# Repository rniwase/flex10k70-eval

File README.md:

# flex10k70-eval
PCB design data for evaluation of the Altera FLEX 10K70 (EPF10K70RC240).

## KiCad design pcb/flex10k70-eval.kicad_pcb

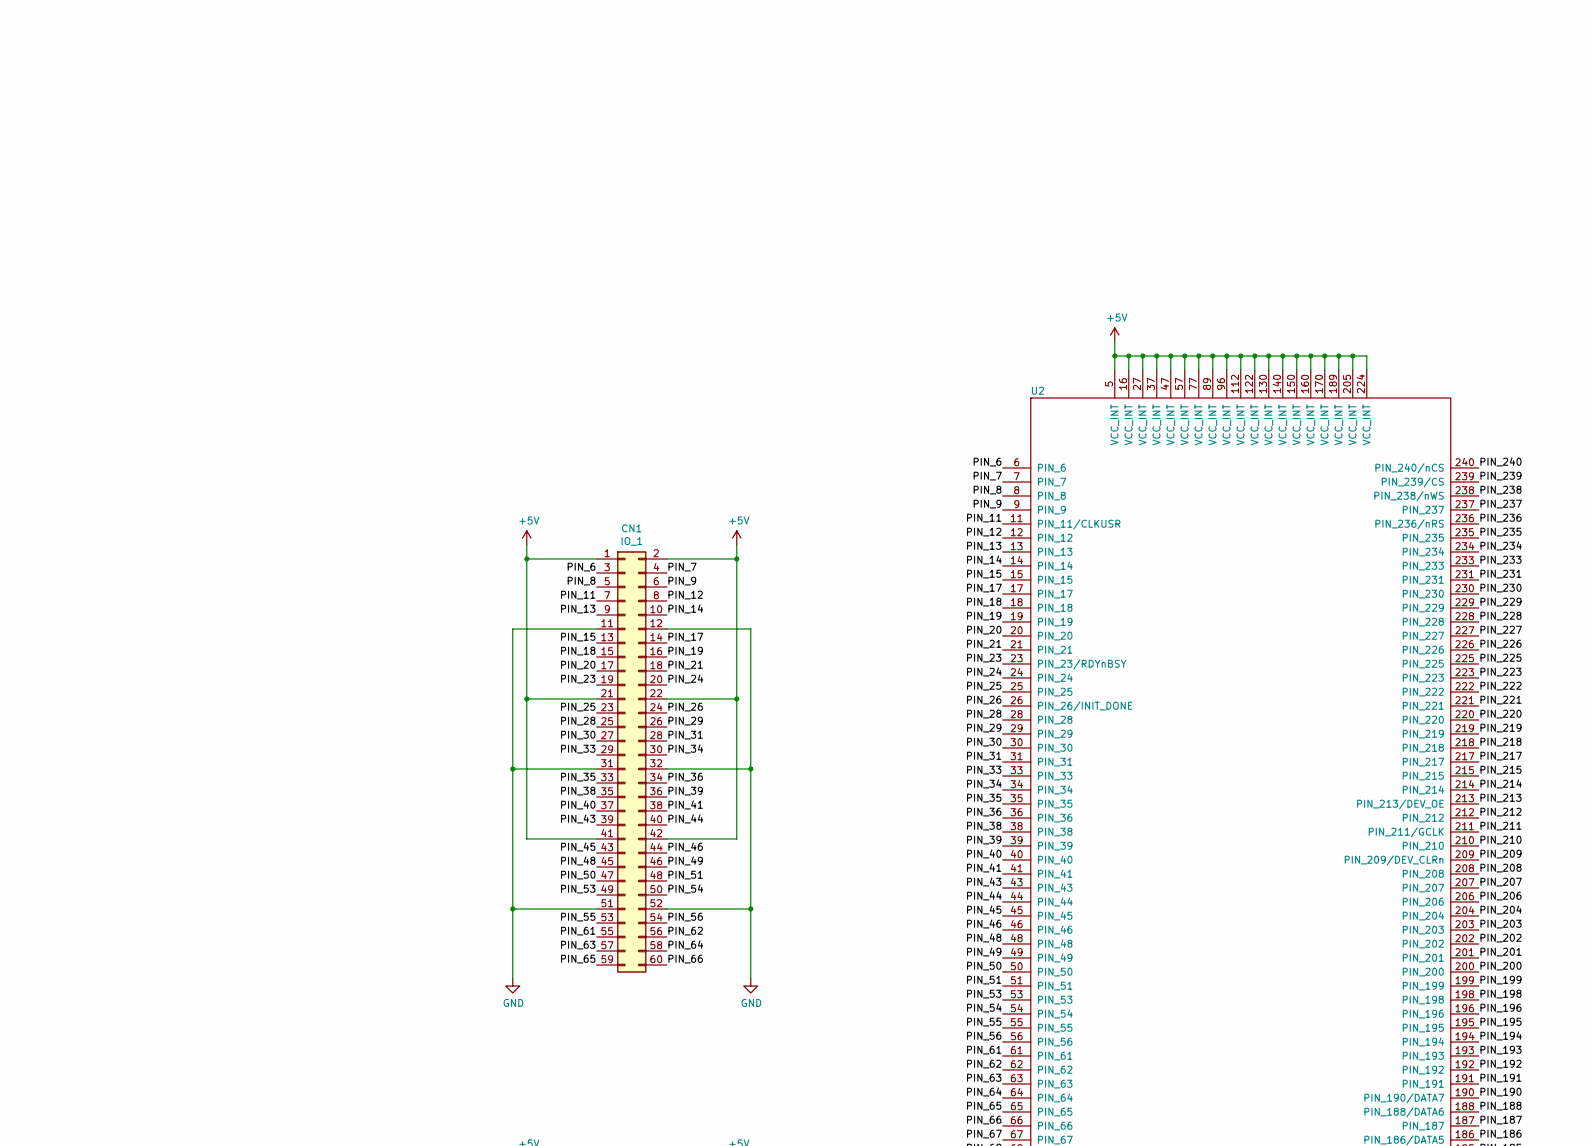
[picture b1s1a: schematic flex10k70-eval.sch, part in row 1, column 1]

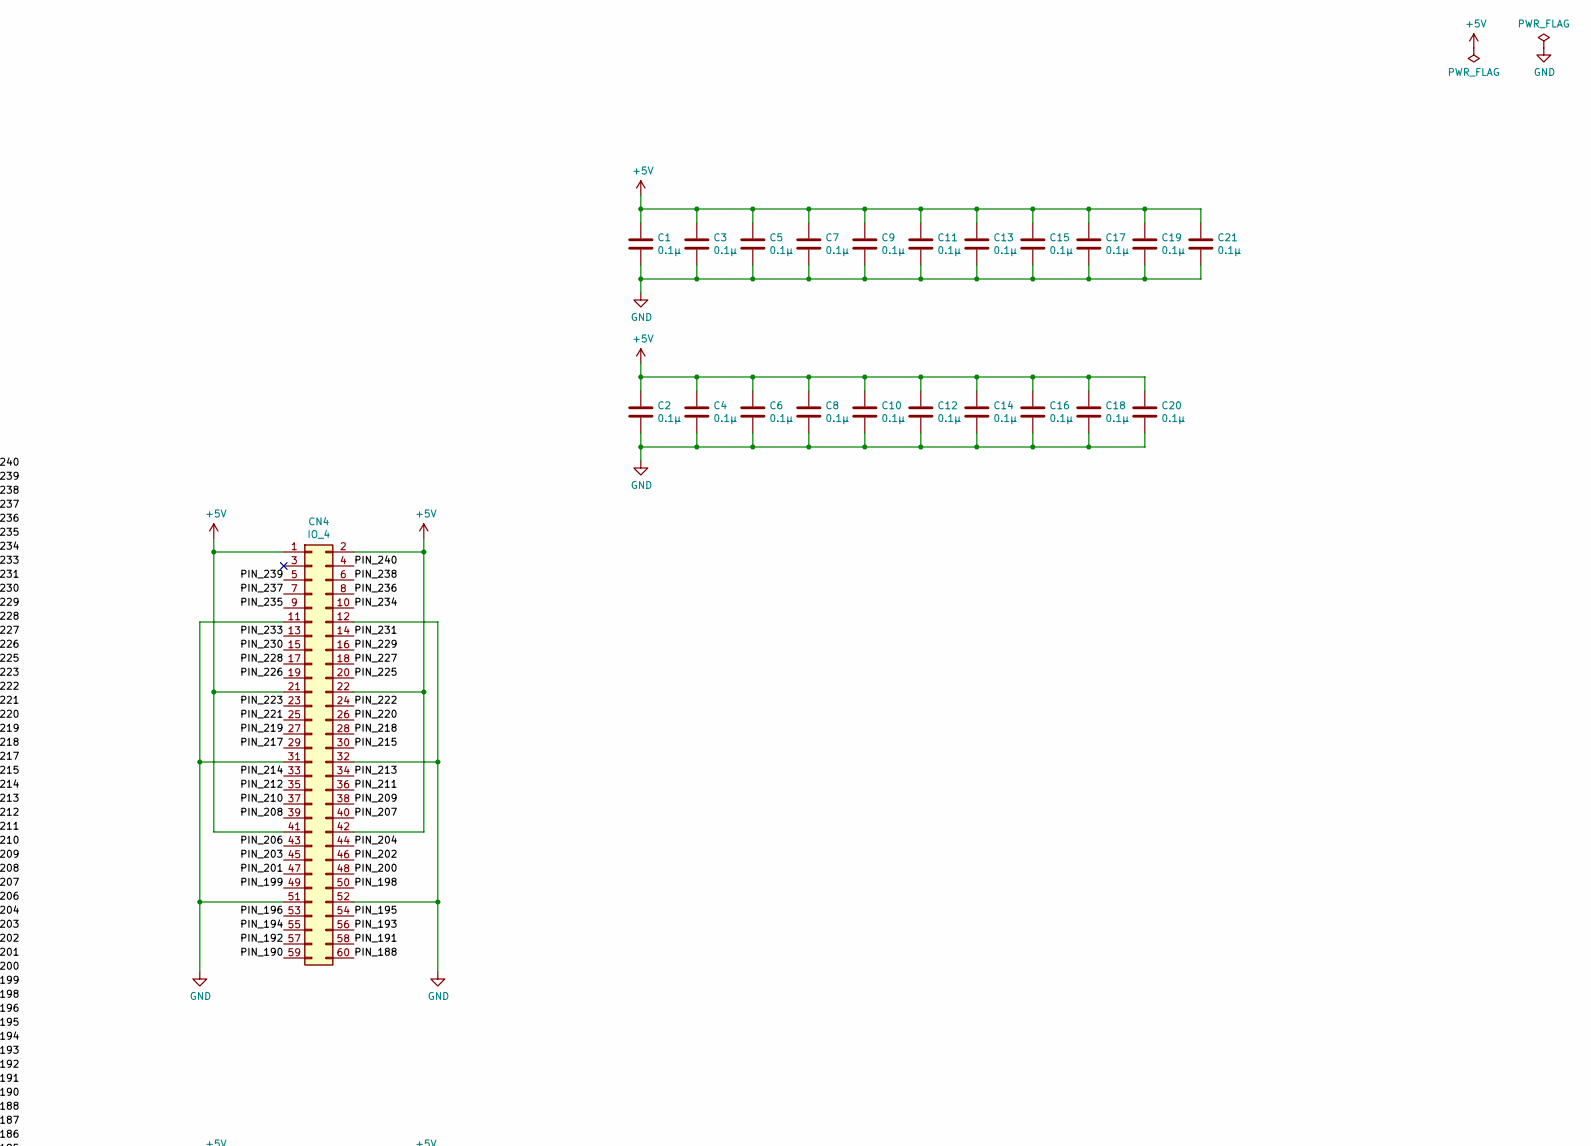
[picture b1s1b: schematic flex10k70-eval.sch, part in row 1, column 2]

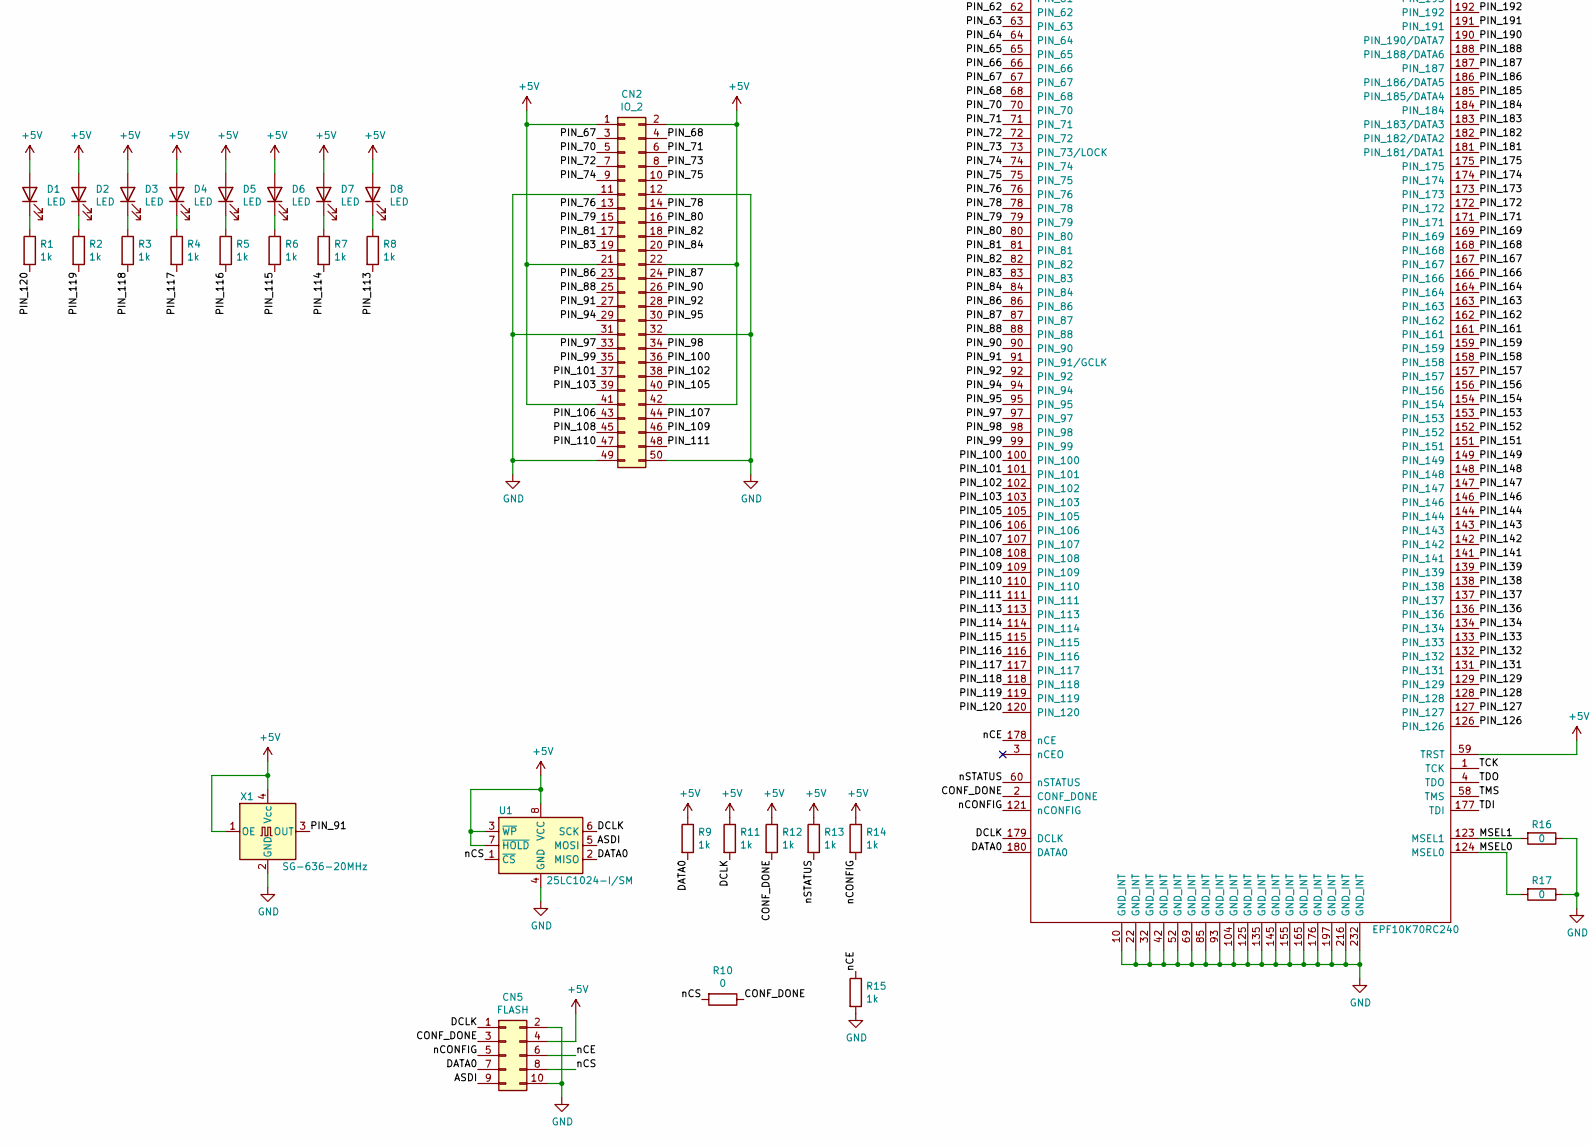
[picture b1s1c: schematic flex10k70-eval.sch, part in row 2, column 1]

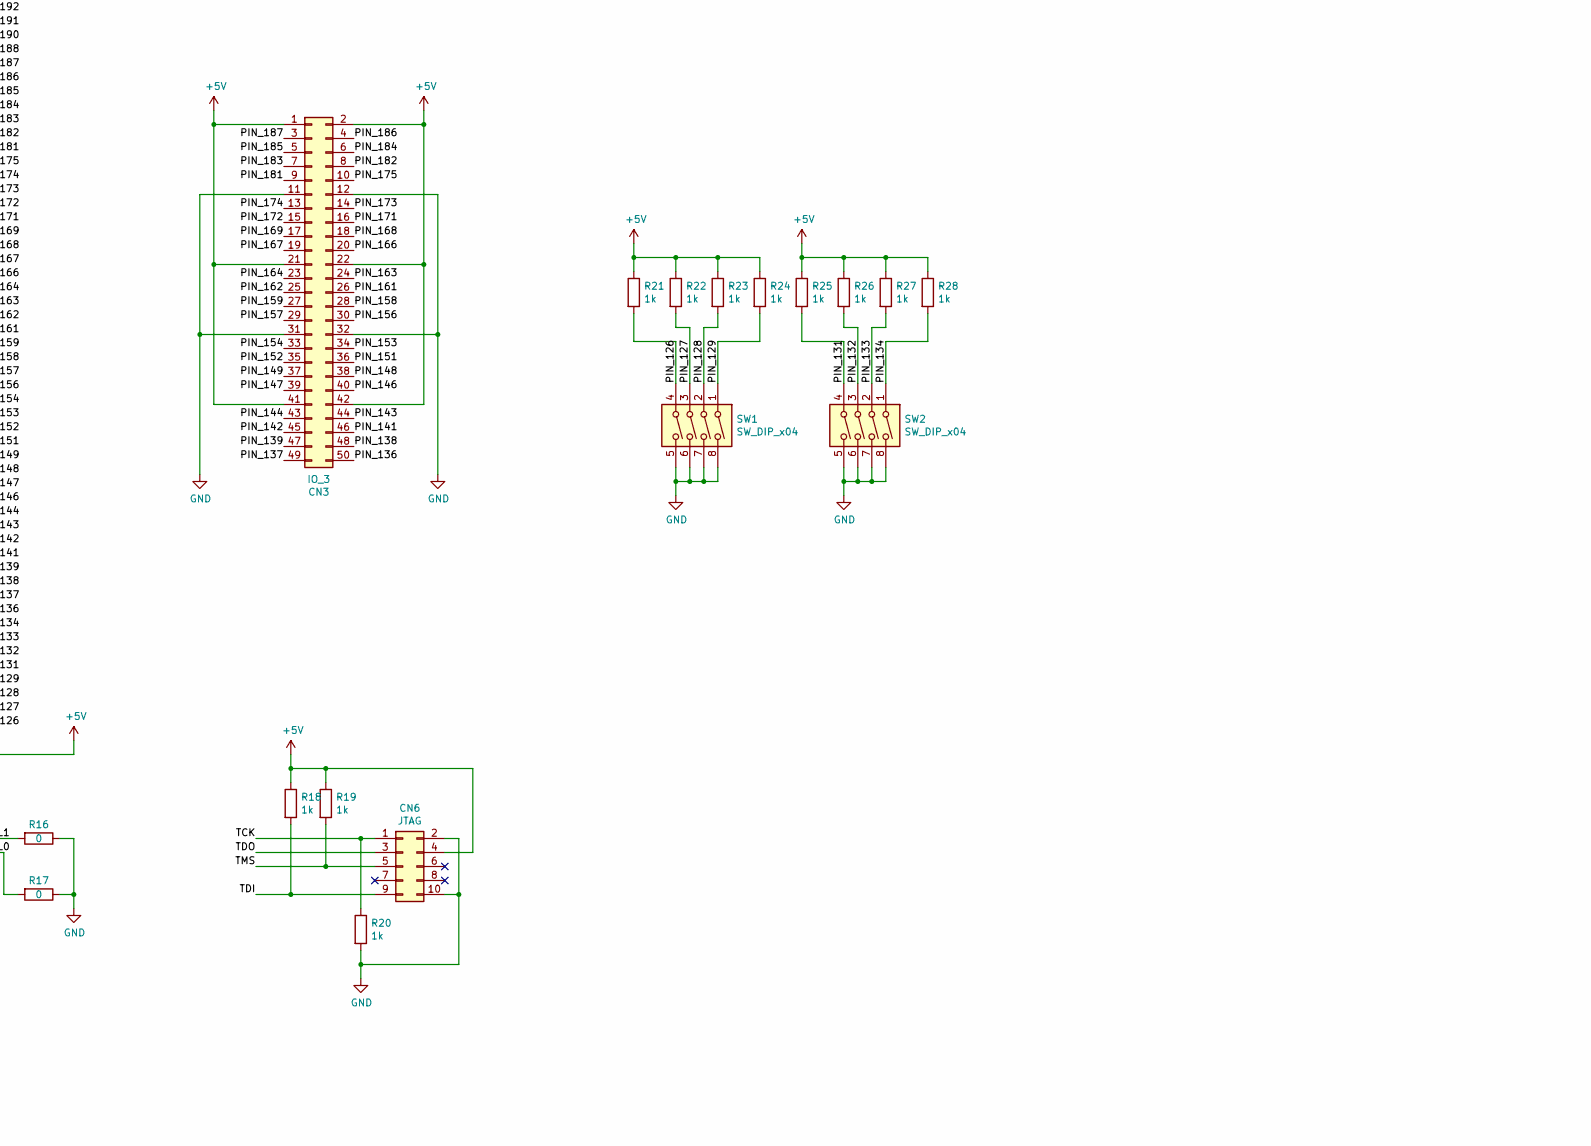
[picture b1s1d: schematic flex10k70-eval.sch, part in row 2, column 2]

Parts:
C1, C2, C3, C4, C5, C6, C7, C8, C9, C10, C11, C12, C13, C14, C15, C16, C17, C18, C19, C20, C21: 0.1μ; C_0603_1608Metric
CN1: IO_1; PinHeader_2x30_P2.54mm_Vertical_SMD
CN2: IO_2; PinHeader_2x25_P2.54mm_Vertical_SMD
CN3: IO_3; PinHeader_2x25_P2.54mm_Vertical_SMD
CN4: IO_4; PinHeader_2x30_P2.54mm_Vertical_SMD
CN5: FLASH; PinHeader_2x05_P2.54mm_Vertical_SMD
CN6: JTAG; PinHeader_2x05_P2.54mm_Vertical_SMD
D1, D2, D3, D4, D5, D6, D7, D8: LED; LED_0603_1608Metric_Castellated
R1, R2, R3, R4, R5, R6, R7, R8, R9, R11, R12, R13, R14, R15, R18, R19, R20, R21, R22, R23, R24, R25, R26, R27, R28: 1k; R_0603_1608Metric
R10, R16, R17: 0; R_0603_1608Metric
SW1, SW2: SW_DIP_x04; SOIJ-8_5.3x5.3mm_P1.27mm
U1: 25LC1024-I/SM; SOIJ-8_5.3x5.3mm_P1.27mm
U2: EPF10K70RC240; PQFP-240_32.1x32.1mm_P0.5mm
X1: SG-636-20MHz; Oscillator_SMD_SeikoEpson_SG8002JC-4Pin_10.5x5.0mm

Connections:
+5V: C1.1, C2.1, C3.1, C4.1, C5.1, C6.1, C7.1, C8.1, C9.1, C10.1, C11.1, C12.1, C13.1, C14.1, C15.1, C16.1, C17.1, C18.1, C19.1, C20.1, C21.1, CN1.1, CN1.2, CN1.21, CN1.22, CN1.41, CN1.42, CN2.1, CN2.2, CN2.21, CN2.22, CN2.41, CN2.42, CN3.1, CN3.2, CN3.21, CN3.22, CN3.41, CN3.42, CN4.1, CN4.2, CN4.21, CN4.22, CN4.41, CN4.42, CN5.4, CN6.4, D1.2 (A), D2.2 (A), D3.2 (A), D4.2 (A), D5.2 (A), D6.2 (A), D7.2 (A), D8.2 (A), R9.1, R11.1, R12.1, R13.1, R14.1, R18.1, R19.1, R21.1, R22.1, R23.1, R24.1, R25.1, R26.1, R27.1, R28.1, U1.3 (~WP), U1.7 (~HOLD), U1.8 (VCC), U2.5 (VCC_INT), U2.16 (VCC_INT), U2.27 (VCC_INT), U2.37 (VCC_INT), U2.47 (VCC_INT), U2.57 (VCC_INT), U2.59 (TRST), U2.77 (VCC_INT), U2.89 (VCC_INT), U2.96 (VCC_INT), U2.112 (VCC_INT), U2.122 (VCC_INT), U2.130 (VCC_INT), U2.140 (VCC_INT), U2.150 (VCC_INT), U2.160 (VCC_INT), U2.170 (VCC_INT), U2.189 (VCC_INT), U2.205 (VCC_INT), U2.224 (VCC_INT), X1.1 (OE), X1.4 (Vcc)
/ASDI: CN5.9, U1.5 (MOSI)
/CONF_DONE: CN5.3, R10.1, R12.2, U2.2 (CONF_DONE)
/DATA0: CN5.7, R9.2, U1.2 (MISO), U2.180 (DATA0)
/DCLK: CN5.1, R11.2, U1.6 (SCK), U2.179 (DCLK)
/MSEL0: R17.2, U2.124 (MSEL0)
/MSEL1: R16.2, U2.123 (MSEL1)
/PIN_6: CN1.3, U2.6 (PIN_6)
/PIN_7: CN1.4, U2.7 (PIN_7)
/PIN_8: CN1.5, U2.8 (PIN_8)
/PIN_9: CN1.6, U2.9 (PIN_9)
/PIN_11: CN1.7, U2.11 (PIN_11/CLKUSR)
/PIN_12: CN1.8, U2.12 (PIN_12)
/PIN_13: CN1.9, U2.13 (PIN_13)
/PIN_14: CN1.10, U2.14 (PIN_14)
/PIN_15: CN1.13, U2.15 (PIN_15)
/PIN_17: CN1.14, U2.17 (PIN_17)
/PIN_18: CN1.15, U2.18 (PIN_18)
/PIN_19: CN1.16, U2.19 (PIN_19)
/PIN_20: CN1.17, U2.20 (PIN_20)
/PIN_21: CN1.18, U2.21 (PIN_21)
/PIN_23: CN1.19, U2.23 (PIN_23/RDYnBSY)
/PIN_24: CN1.20, U2.24 (PIN_24)
/PIN_25: CN1.23, U2.25 (PIN_25)
/PIN_26: CN1.24, U2.26 (PIN_26/INIT_DONE)
/PIN_28: CN1.25, U2.28 (PIN_28)
/PIN_29: CN1.26, U2.29 (PIN_29)
/PIN_30: CN1.27, U2.30 (PIN_30)
/PIN_31: CN1.28, U2.31 (PIN_31)
/PIN_33: CN1.29, U2.33 (PIN_33)
/PIN_34: CN1.30, U2.34 (PIN_34)
/PIN_35: CN1.33, U2.35 (PIN_35)
/PIN_36: CN1.34, U2.36 (PIN_36)
/PIN_38: CN1.35, U2.38 (PIN_38)
/PIN_39: CN1.36, U2.39 (PIN_39)
/PIN_40: CN1.37, U2.40 (PIN_40)
/PIN_41: CN1.38, U2.41 (PIN_41)
/PIN_43: CN1.39, U2.43 (PIN_43)
/PIN_44: CN1.40, U2.44 (PIN_44)
/PIN_45: CN1.43, U2.45 (PIN_45)
/PIN_46: CN1.44, U2.46 (PIN_46)
/PIN_48: CN1.45, U2.48 (PIN_48)
/PIN_49: CN1.46, U2.49 (PIN_49)
/PIN_50: CN1.47, U2.50 (PIN_50)
/PIN_51: CN1.48, U2.51 (PIN_51)
/PIN_53: CN1.49, U2.53 (PIN_53)
/PIN_54: CN1.50, U2.54 (PIN_54)
/PIN_55: CN1.53, U2.55 (PIN_55)
/PIN_56: CN1.54, U2.56 (PIN_56)
/PIN_61: CN1.55, U2.61 (PIN_61)
/PIN_62: CN1.56, U2.62 (PIN_62)
/PIN_63: CN1.57, U2.63 (PIN_63)
/PIN_64: CN1.58, U2.64 (PIN_64)
/PIN_65: CN1.59, U2.65 (PIN_65)
/PIN_66: CN1.60, U2.66 (PIN_66)
/PIN_67: CN2.3, U2.67 (PIN_67)
/PIN_68: CN2.4, U2.68 (PIN_68)
/PIN_70: CN2.5, U2.70 (PIN_70)
/PIN_71: CN2.6, U2.71 (PIN_71)
/PIN_72: CN2.7, U2.72 (PIN_72)
/PIN_73: CN2.8, U2.73 (PIN_73/LOCK)
/PIN_74: CN2.9, U2.74 (PIN_74)
/PIN_75: CN2.10, U2.75 (PIN_75)
/PIN_76: CN2.13, U2.76 (PIN_76)
/PIN_78: CN2.14, U2.78 (PIN_78)
/PIN_79: CN2.15, U2.79 (PIN_79)
/PIN_80: CN2.16, U2.80 (PIN_80)
/PIN_81: CN2.17, U2.81 (PIN_81)
/PIN_82: CN2.18, U2.82 (PIN_82)
/PIN_83: CN2.19, U2.83 (PIN_83)
/PIN_84: CN2.20, U2.84 (PIN_84)
/PIN_86: CN2.23, U2.86 (PIN_86)
/PIN_87: CN2.24, U2.87 (PIN_87)
/PIN_88: CN2.25, U2.88 (PIN_88)
/PIN_90: CN2.26, U2.90 (PIN_90)
/PIN_91: CN2.27, U2.91 (PIN_91/GCLK), X1.3 (OUT)
/PIN_92: CN2.28, U2.92 (PIN_92)
/PIN_94: CN2.29, U2.94 (PIN_94)
/PIN_95: CN2.30, U2.95 (PIN_95)
/PIN_97: CN2.33, U2.97 (PIN_97)
/PIN_98: CN2.34, U2.98 (PIN_98)
/PIN_99: CN2.35, U2.99 (PIN_99)
/PIN_100: CN2.36, U2.100 (PIN_100)
/PIN_101: CN2.37, U2.101 (PIN_101)
/PIN_102: CN2.38, U2.102 (PIN_102)
/PIN_103: CN2.39, U2.103 (PIN_103)
/PIN_105: CN2.40, U2.105 (PIN_105)
/PIN_106: CN2.43, U2.106 (PIN_106)
/PIN_107: CN2.44, U2.107 (PIN_107)
/PIN_108: CN2.45, U2.108 (PIN_108)
/PIN_109: CN2.46, U2.109 (PIN_109)
/PIN_110: CN2.47, U2.110 (PIN_110)
/PIN_111: CN2.48, U2.111 (PIN_111)
/PIN_113: R8.2, U2.113 (PIN_113)
/PIN_114: R7.2, U2.114 (PIN_114)
/PIN_115: R6.2, U2.115 (PIN_115)
/PIN_116: R5.2, U2.116 (PIN_116)
/PIN_117: R4.2, U2.117 (PIN_117)
/PIN_118: R3.2, U2.118 (PIN_118)
/PIN_119: R2.2, U2.119 (PIN_119)
/PIN_120: R1.2, U2.120 (PIN_120)
/PIN_126: R21.2, SW1.4, U2.126 (PIN_126)
/PIN_127: R22.2, SW1.3, U2.127 (PIN_127)
/PIN_128: R23.2, SW1.2, U2.128 (PIN_128)
/PIN_129: R24.2, SW1.1, U2.129 (PIN_129)
/PIN_131: R25.2, SW2.4, U2.131 (PIN_131)
/PIN_132: R26.2, SW2.3, U2.132 (PIN_132)
/PIN_133: R27.2, SW2.2, U2.133 (PIN_133)
/PIN_134: R28.2, SW2.1, U2.134 (PIN_134)
/PIN_136: CN3.50, U2.136 (PIN_136)
/PIN_137: CN3.49, U2.137 (PIN_137)
/PIN_138: CN3.48, U2.138 (PIN_138)
/PIN_139: CN3.47, U2.139 (PIN_139)
/PIN_141: CN3.46, U2.141 (PIN_141)
/PIN_142: CN3.45, U2.142 (PIN_142)
/PIN_143: CN3.44, U2.143 (PIN_143)
/PIN_144: CN3.43, U2.144 (PIN_144)
/PIN_146: CN3.40, U2.146 (PIN_146)
/PIN_147: CN3.39, U2.147 (PIN_147)
/PIN_148: CN3.38, U2.148 (PIN_148)
/PIN_149: CN3.37, U2.149 (PIN_149)
/PIN_151: CN3.36, U2.151 (PIN_151)
/PIN_152: CN3.35, U2.152 (PIN_152)
/PIN_153: CN3.34, U2.153 (PIN_153)
/PIN_154: CN3.33, U2.154 (PIN_154)
/PIN_156: CN3.30, U2.156 (PIN_156)
/PIN_157: CN3.29, U2.157 (PIN_157)
/PIN_158: CN3.28, U2.158 (PIN_158)
/PIN_159: CN3.27, U2.159 (PIN_159)
/PIN_161: CN3.26, U2.161 (PIN_161)
/PIN_162: CN3.25, U2.162 (PIN_162)
/PIN_163: CN3.24, U2.163 (PIN_163)
/PIN_164: CN3.23, U2.164 (PIN_164)
/PIN_166: CN3.20, U2.166 (PIN_166)
/PIN_167: CN3.19, U2.167 (PIN_167)
/PIN_168: CN3.18, U2.168 (PIN_168)
/PIN_169: CN3.17, U2.169 (PIN_169)
/PIN_171: CN3.16, U2.171 (PIN_171)
/PIN_172: CN3.15, U2.172 (PIN_172)
/PIN_173: CN3.14, U2.173 (PIN_173)
/PIN_174: CN3.13, U2.174 (PIN_174)
/PIN_175: CN3.10, U2.175 (PIN_175)
/PIN_181: CN3.9, U2.181 (PIN_181/DATA1)
/PIN_182: CN3.8, U2.182 (PIN_182/DATA2)
/PIN_183: CN3.7, U2.183 (PIN_183/DATA3)
/PIN_184: CN3.6, U2.184 (PIN_184)
/PIN_185: CN3.5, U2.185 (PIN_185/DATA4)
/PIN_186: CN3.4, U2.186 (PIN_186/DATA5)
/PIN_187: CN3.3, U2.187 (PIN_187)
/PIN_188: CN4.60, U2.188 (PIN_188/DATA6)
/PIN_190: CN4.59, U2.190 (PIN_190/DATA7)
/PIN_191: CN4.58, U2.191 (PIN_191)
/PIN_192: CN4.57, U2.192 (PIN_192)
/PIN_193: CN4.56, U2.193 (PIN_193)
/PIN_194: CN4.55, U2.194 (PIN_194)
/PIN_195: CN4.54, U2.195 (PIN_195)
/PIN_196: CN4.53, U2.196 (PIN_196)
/PIN_198: CN4.50, U2.198 (PIN_198)
/PIN_199: CN4.49, U2.199 (PIN_199)
/PIN_200: CN4.48, U2.200 (PIN_200)
/PIN_201: CN4.47, U2.201 (PIN_201)
/PIN_202: CN4.46, U2.202 (PIN_202)
/PIN_203: CN4.45, U2.203 (PIN_203)
/PIN_204: CN4.44, U2.204 (PIN_204)
/PIN_206: CN4.43, U2.206 (PIN_206)
/PIN_207: CN4.40, U2.207 (PIN_207)
/PIN_208: CN4.39, U2.208 (PIN_208)
/PIN_209: CN4.38, U2.209 (PIN_209/DEV_CLRn)
/PIN_210: CN4.37, U2.210 (PIN_210)
/PIN_211: CN4.36, U2.211 (PIN_211/GCLK)
/PIN_212: CN4.35, U2.212 (PIN_212)
/PIN_213: CN4.34, U2.213 (PIN_213/DEV_OE)
/PIN_214: CN4.33, U2.214 (PIN_214)
/PIN_215: CN4.30, U2.215 (PIN_215)
/PIN_217: CN4.29, U2.217 (PIN_217)
/PIN_218: CN4.28, U2.218 (PIN_218)
/PIN_219: CN4.27, U2.219 (PIN_219)
/PIN_220: CN4.26, U2.220 (PIN_220)
/PIN_221: CN4.25, U2.221 (PIN_221)
/PIN_222: CN4.24, U2.222 (PIN_222)
/PIN_223: CN4.23, U2.223 (PIN_223)
/PIN_225: CN4.20, U2.225 (PIN_225)
/PIN_226: CN4.19, U2.226 (PIN_226)
/PIN_227: CN4.18, U2.227 (PIN_227)
/PIN_228: CN4.17, U2.228 (PIN_228)
/PIN_229: CN4.16, U2.229 (PIN_229)
/PIN_230: CN4.15, U2.230 (PIN_230)
/PIN_231: CN4.14, U2.231 (PIN_231)
/PIN_233: CN4.13, U2.233 (PIN_233)
/PIN_234: CN4.10, U2.234 (PIN_234)
/PIN_235: CN4.9, U2.235 (PIN_235)
/PIN_236: CN4.8, U2.236 (PIN_236/nRS)
/PIN_237: CN4.7, U2.237 (PIN_237)
/PIN_238: CN4.6, U2.238 (PIN_238/nWS)
/PIN_239: CN4.5, U2.239 (PIN_239/CS)
/PIN_240: CN4.4, U2.240 (PIN_240/nCS)
/TCK: CN6.1, R20.1, U2.1 (TCK)
/TDI: CN6.9, R18.2, U2.177 (TDI)
/TDO: CN6.3, U2.4 (TDO)
/TMS: CN6.5, R19.2, U2.58 (TMS)
/nCE: CN5.6, R15.1, U2.178 (nCE)
/nCONFIG: CN5.5, R14.2, U2.121 (nCONFIG)
/nCS: CN5.8, R10.2, U1.1 (~CS)
/nSTATUS: R13.2, U2.60 (nSTATUS)
GND: C1.2, C2.2, C3.2, C4.2, C5.2, C6.2, C7.2, C8.2, C9.2, C10.2, C11.2, C12.2, C13.2, C14.2, C15.2, C16.2, C17.2, C18.2, C19.2, C20.2, C21.2, CN1.11, CN1.12, CN1.31, CN1.32, CN1.51, CN1.52, CN2.11, CN2.12, CN2.31, CN2.32, CN2.49, CN2.50, CN3.11, CN3.12, CN3.31, CN3.32, CN4.11, CN4.12, CN4.31, CN4.32, CN4.51, CN4.52, CN5.2, CN5.10, CN6.2, CN6.10, R15.2, R16.1, R17.1, R20.2, SW1.5, SW1.6, SW1.7, SW1.8, SW2.5, SW2.6, SW2.7, SW2.8, U1.4 (GND), U2.10 (GND_INT), U2.22 (GND_INT), U2.32 (GND_INT), U2.42 (GND_INT), U2.52 (GND_INT), U2.69 (GND_INT), U2.85 (GND_INT), U2.93 (GND_INT), U2.104 (GND_INT), U2.125 (GND_INT), U2.135 (GND_INT), U2.145 (GND_INT), U2.155 (GND_INT), U2.165 (GND_INT), U2.176 (GND_INT), U2.197 (GND_INT), U2.216 (GND_INT), U2.232 (GND_INT), X1.2 (GND)
unnamed: D1.1 (K), R1.1
unnamed: D2.1 (K), R2.1
unnamed: D3.1 (K), R3.1
unnamed: D4.1 (K), R4.1
unnamed: D5.1 (K), R5.1
unnamed: D6.1 (K), R6.1
unnamed: D7.1 (K), R7.1
unnamed: D8.1 (K), R8.1

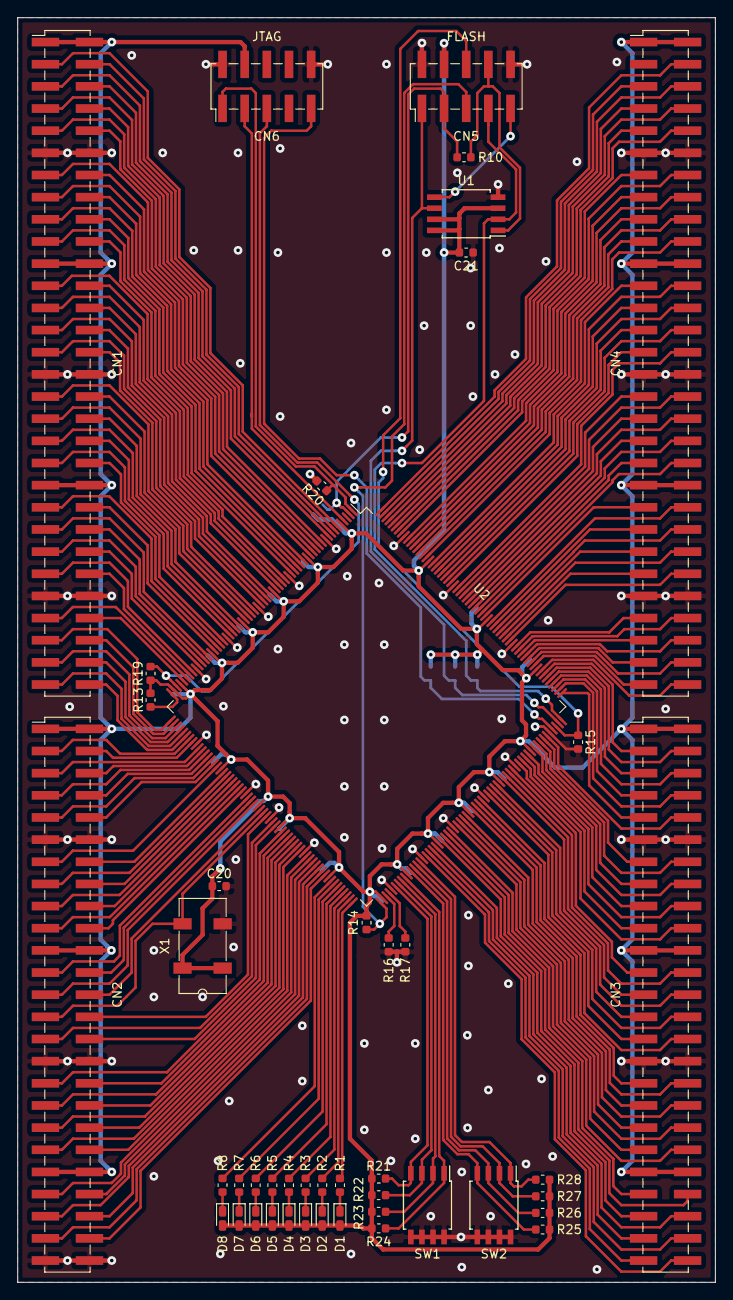
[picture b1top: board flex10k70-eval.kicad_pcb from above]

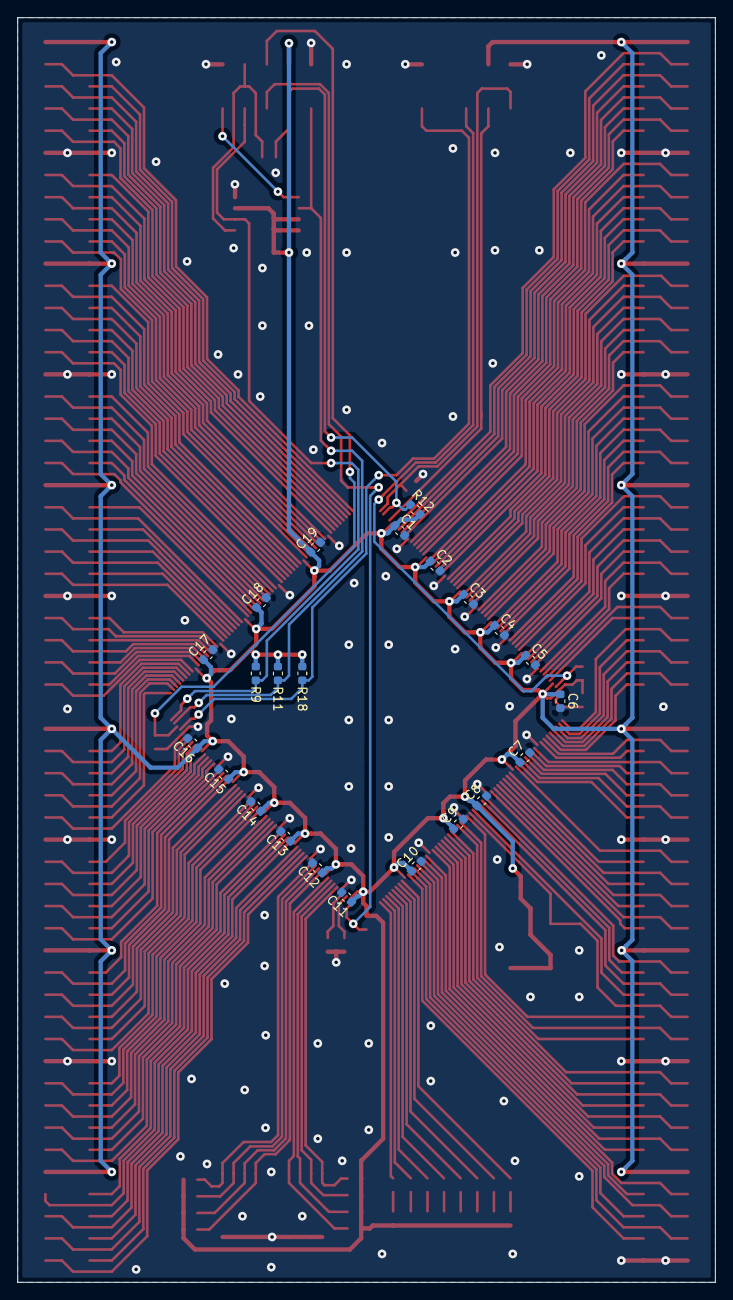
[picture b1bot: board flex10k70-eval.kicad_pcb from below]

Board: 2 copper layers, 80.0 x 145.0 mm, 68 parts (23 on the bottom side), 213 nets.

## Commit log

2020-08-25 modify CN3 CN4 pin orientation
2020-08-25 modify GND via
2020-08-28 modify gnd via, silk, plot gerber, drill
2020-09-10 add g-code
2020-12-11 add .gitattributes
